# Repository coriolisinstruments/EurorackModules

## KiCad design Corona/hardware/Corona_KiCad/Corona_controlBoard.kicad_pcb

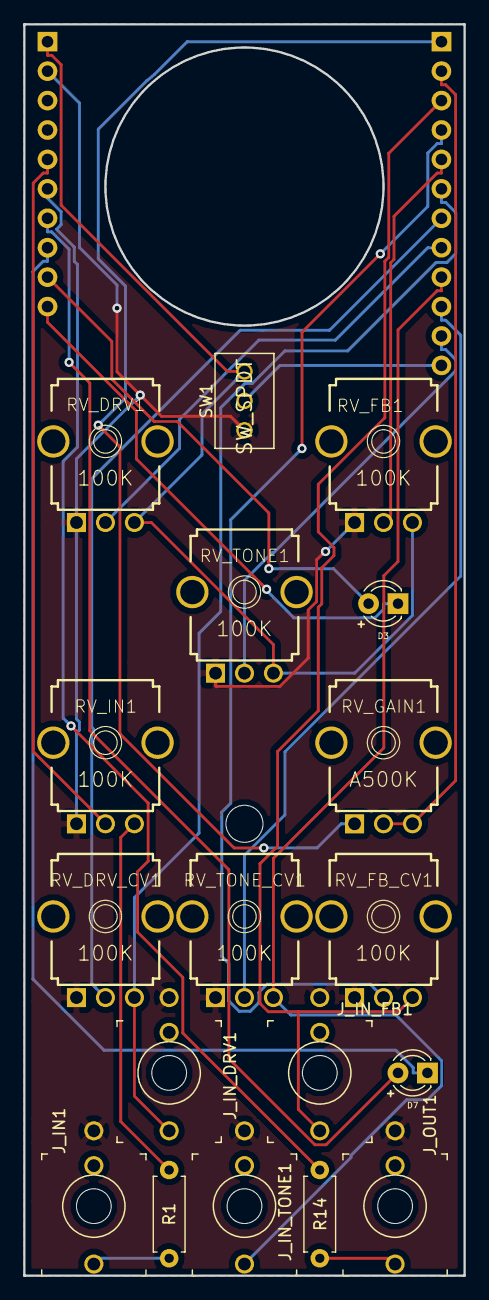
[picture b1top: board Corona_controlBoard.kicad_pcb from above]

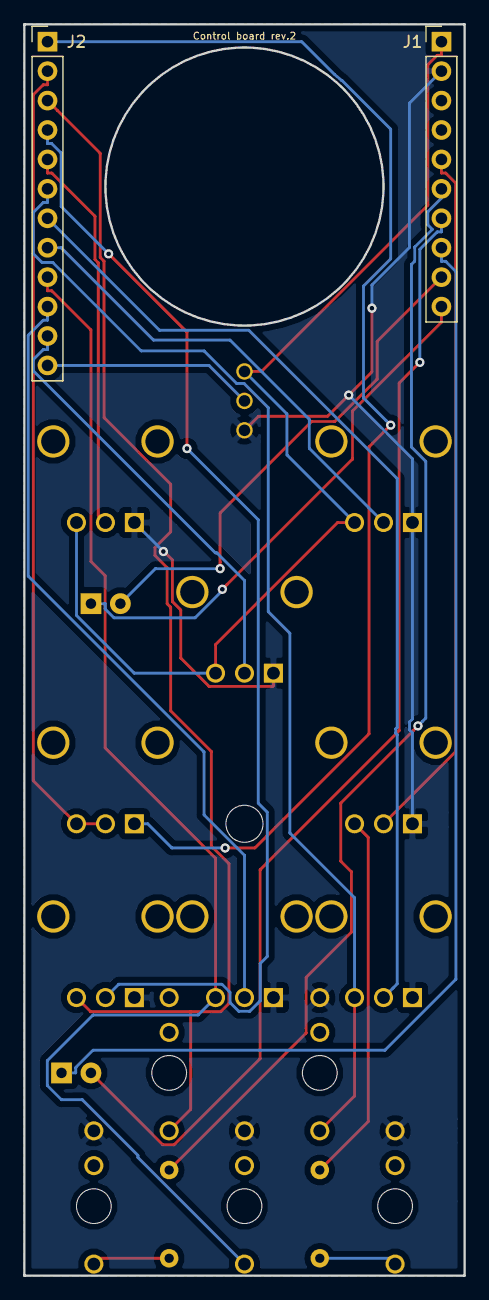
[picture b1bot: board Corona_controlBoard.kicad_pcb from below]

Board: 2 copper layers, 38.0 x 108.0 mm, 22 parts (2 on the bottom side), 23 nets.

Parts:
D3, D7: LED; LED_D3.0mm_smalltext
J1: Conn_01x10; PinHeader_1x10_P2.54mm_Vertical
J2: Conn_01x12; PinHeader_1x12_P2.54mm_Vertical
J_IN1: Audio-Jack-2_Switch; WQP-PJ301M-12_JACK
J_IN_DRV1: Audio-Jack-2_Switch; WQP-PJ301M-12_JACK
J_IN_FB1: Audio-Jack-2_Switch; WQP-PJ301M-12_JACK
J_IN_TONE1: Audio-Jack-2_Switch; WQP-PJ301M-12_JACK
J_OUT1: Audio-Jack-2_Switch; WQP-PJ301M-12_JACK
MK3: Mounting_Hole; MountingHole_3.2mm_M3
MK5: CoriolisLogo; art_Coriolis_logo_copper
R1: 47K; R_Axial_DIN0207_L6.3mm_D2.5mm_P7.62mm_Horizontal
R14: 470r; R_Axial_DIN0207_L6.3mm_D2.5mm_P7.62mm_Horizontal
RV_DRV1: 100K; 9MM_SNAP-IN_POT
RV_DRV_CV1: 100K; 9MM_SNAP-IN_POT
RV_FB1: 100K; 9MM_SNAP-IN_POT
RV_FB_CV1: 100K; 9MM_SNAP-IN_POT
RV_GAIN1: A500K; 9MM_SNAP-IN_POT
RV_IN1: 100K; 9MM_SNAP-IN_POT
RV_TONE1: 100K; 9MM_SNAP-IN_POT
RV_TONE_CV1: 100K; 9MM_SNAP-IN_POT
SW1: SW_SPDT; SUBMINI_TOGGLE

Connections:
/+12V.cb: J1.1, RV_DRV1.3, RV_FB1.3, RV_TONE1.3, SW1.3
/R.gain.1.cb: J2.1, RV_GAIN1.1
/R.gain.3.cb: J2.2, RV_GAIN1.2, RV_GAIN1.3
/audio.in.cb: J1.5, RV_IN1.2
/audio.out.cb: J1.6, R14.2
/drv.cv.in.cb: J2.6, J_IN_DRV1.1, RV_DRV_CV1.3
/drv.cv.level.cb: J2.7, RV_DRV_CV1.2
/drv.level.cb: J2.8, RV_DRV1.2
/fb.cv.in.cb: J2.3, J_IN_FB1.1, RV_FB_CV1.3
/fb.cv.level.cb: J2.4, RV_FB_CV1.2
/fb.level.cb: J2.5, RV_FB1.2
/gnd.cb: J1.2, J_IN1.2, J_IN_DRV1.2, J_IN_FB1.2, J_IN_TONE1.2, J_OUT1.2, RV_DRV1.1, RV_DRV_CV1.1, RV_FB1.1, RV_FB_CV1.1, RV_IN1.1, RV_TONE1.1, RV_TONE_CV1.1, SW1.1
/led.clip.in.cb: D7.2, J1.7
/led.clip.out.cb: D7.1, J1.8
/led.fb.in.cb: D3.2, J1.9
/led.fb.out.cb: D3.1, J1.10
/tone.cv.in.cb: J2.9, J_IN_TONE1.1, RV_TONE_CV1.3
/tone.cv.level.cb: J2.10, RV_TONE_CV1.2
/tone.level.cb: J2.11, RV_TONE1.2
/tube.gnd.cb: J2.12, SW1.2
unnamed: J_IN1.1, R1.2
unnamed: J_OUT1.1, R14.1
unnamed: R1.1, RV_IN1.3

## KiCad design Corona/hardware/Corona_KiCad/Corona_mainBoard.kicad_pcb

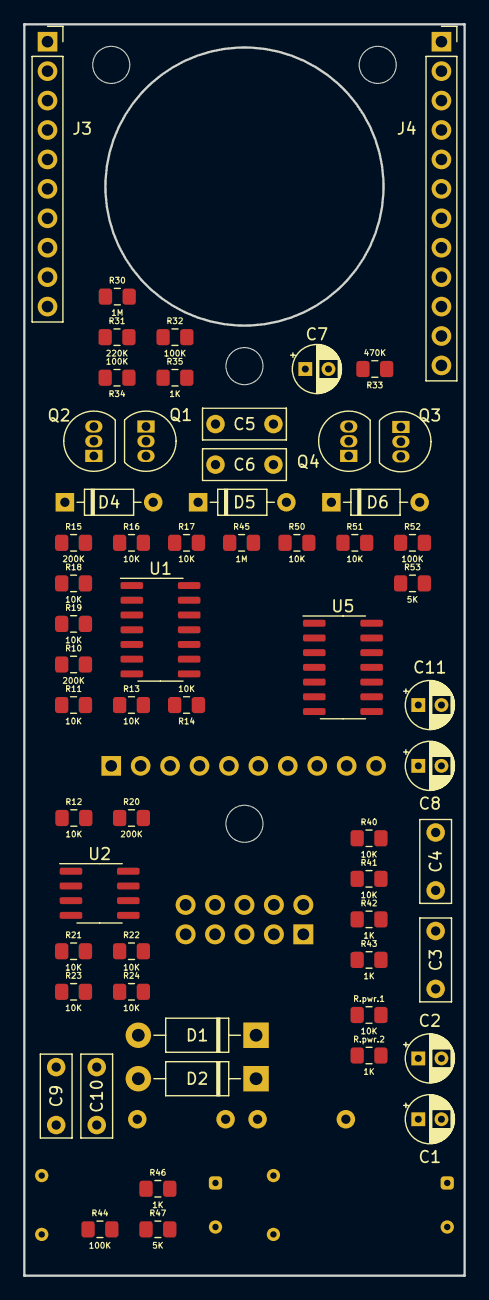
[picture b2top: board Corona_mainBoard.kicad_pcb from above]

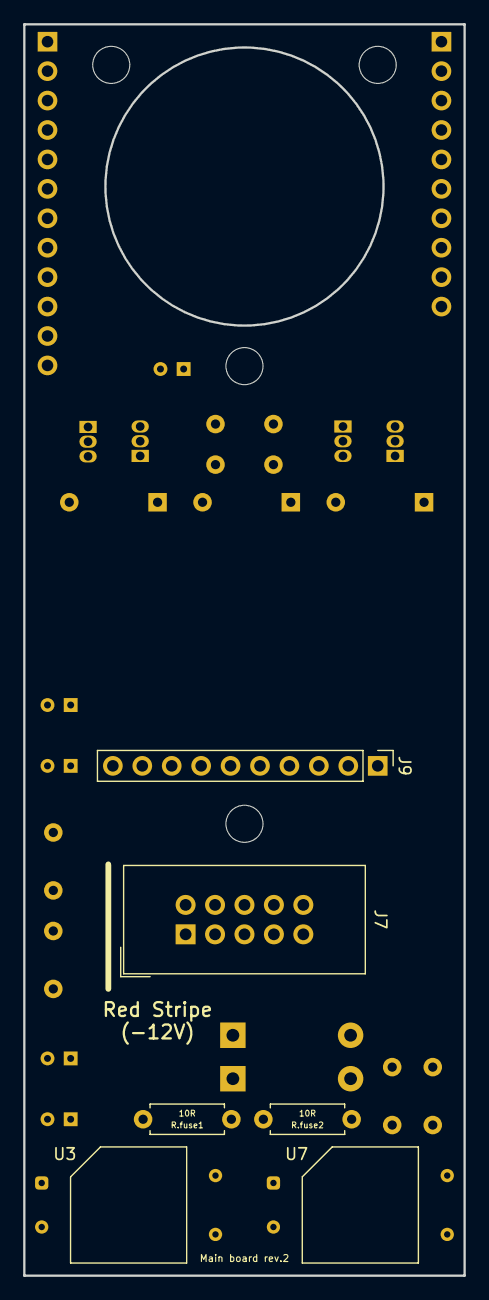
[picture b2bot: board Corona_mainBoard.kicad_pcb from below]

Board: 2 copper layers, 38.0 x 108.0 mm, 70 parts (6 on the bottom side), 55 nets, no tracks yet.

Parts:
C1, C2: 10uF (25V); CP_Radial_D4.0mm_P2.00mm
C3, C4, C10: 100nF; C_Disc_D7.0mm_W2.5mm_P5.00mm
C5, C6: 47nF; C_Disc_D7.0mm_W2.5mm_P5.00mm
C7, C8: 1uF (25V); CP_Radial_D4.0mm_P2.00mm
C9: 22nF; C_Disc_D7.0mm_W2.5mm_P5.00mm
C11: 0.22uF; CP_Radial_D4.0mm_P2.00mm
D1, D2: IN4001; D_DO-41_SOD81_P10.16mm_Horizontal
D4, D5, D6: IN4148; D_DO-35_SOD27_P7.62mm_Horizontal
J3: Conn_01x10; PinSocket_1x10_P2.54mm_Vertical
J4: Conn_01x12; PinSocket_1x12_P2.54mm_Vertical
J7: Conn_02x05_Odd_Even; IDC-Header_2x05_P2.54mm_Vertical
J9: Conn_01x10; PinHeader_1x10_P2.54mm_Vertical
MK.mb1, MK.mb2, MK.mb3, MK.mb4: Mounting_Hole; MountingHole_3.2mm_M3
Q1, Q2, Q3: BC547; TO-92_Inline
Q4: BC557; TO-92_Inline
R10, R15, R20: 200K; R_0805_2012Metric_Pad1.15x1.40mm_HandSolder_smalltext
R11, R12, R13, R14, R16, R17, R18, R19, R21, R22, R23, R24, R40, R41, R50, R51, R.pwr.1: 10K; R_0805_2012Metric_Pad1.15x1.40mm_HandSolder_smalltext
R30, R45: 1M; R_0805_2012Metric_Pad1.15x1.40mm_HandSolder_smalltext
R31: 220K; R_0805_2012Metric_Pad1.15x1.40mm_HandSolder_smalltext
R32, R34, R44, R52: 100K; R_0805_2012Metric_Pad1.15x1.40mm_HandSolder_smalltext
R33: 470K; R_0805_2012Metric_Pad1.15x1.40mm_HandSolder_smalltext
R35, R42, R43, R46, R.pwr.2: 1K; R_0805_2012Metric_Pad1.15x1.40mm_HandSolder_smalltext
R47, R53: 5K; R_0805_2012Metric_Pad1.15x1.40mm_HandSolder_smalltext
R.fuse1, R.fuse2: 10R; R_Axial_DIN0207_smalltext
U1, U5: TL074; SOIC-14_3.9x8.7mm_P1.27mm
U2: TL072; SOIC-8_3.9x4.9mm_P1.27mm
U3, U7: VTL5C; PerkinElmer_VTL5C

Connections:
/+1V: R16.1, R17.1, R21.1, R22.1, R.pwr.1.1, R.pwr.2.2, U1.12, U2.5
/+12V: C1.1, C3.1, D4.2, J3.1, J9.9, Q2.1, Q3.1, R31.2, R34.2, R.fuse1.1, R.pwr.1.2, U1.4, U2.8, U5.4
/-12V: C2.2, C4.2, J3.3, J9.8, R.fuse2.1, U1.11, U2.4, U5.11
/R.gain.1: C8.1, J4.1, U5.1
/R.gain.3: J4.2, R35.1, U5.2
/audio.in: J3.5, U5.5
/audio.out: C10.2, J3.6, J9.10, U5.13, U5.14
/cv.drv: R18.1, U1.14, U3.2
/cv.fb: R13.1, R45.1, U1.8
/cv.tone: R23.1, U2.7, U7.2
/drv.cv.in: J4.6, R15.2, U1.2
/drv.cv.level: J4.7, U1.3
/drv.level: J4.8, R17.2
/fb.cv.in: J4.3, R10.2, U1.6
/fb.cv.level: J4.4, U1.5
/fb.level: J4.5, R12.2
/gnd: C1.2, C2.1, C3.2, C4.1, C11.2, D1.2, D2.1, J3.2, J7.3, J7.4, J7.5, J7.6, J7.7, J7.8, J9.7, R14.1, R19.1, R24.1, R32.1, R40.2, R44.1, R46.1, R47.1, R52.1, R53.1, R.pwr.2.1, U5.3, U5.10, U7.3
/led.clip.in: D6.1, J3.7, Q4.3
/led.clip.out: J3.8, Q4.1, R53.2
/led.fb.in: C9.1, J3.9, Q1.3, R46.2
/led.fb.out: J3.10, R47.2
/tone.cv.in: J4.9, R20.2, U2.2
/tone.cv.level: J4.10, U2.3
/tone.level: J4.11, R22.2
/tube.1: C6.2, J9.1, R31.1
/tube.2: C5.1, J9.2, R30.2
/tube.3: J9.3, U3.4
/tube.6: C7.1, J9.4, R34.1
/tube.7: C6.1, J9.5, R33.2
/tube.8: J4.12, J9.6, R30.1, R33.1, U3.3
/tube.in: C5.2, C9.2, R41.1, U5.7
/tube.out: C8.2, R42.2, R50.2
unnamed: C7.2, R35.2
unnamed: C10.1, U7.4
unnamed: C11.1, Q3.3, R51.2, R52.2
unnamed: D1.1, J7.9, J7.10, R.fuse1.2
unnamed: D2.2, J7.1, J7.2, R.fuse2.2
unnamed: D4.1, D5.2
unnamed: D5.1, D6.2
unnamed: Q1.1, R43.1, U5.8, U5.12
unnamed: Q1.2, Q2.3
unnamed: Q2.2, R45.2
unnamed: Q3.2, R50.1
unnamed: Q4.2, R51.1
unnamed: R10.1, R11.2, U1.7
unnamed: R11.1, R12.1, U1.10
unnamed: R13.2, R14.2, U1.9
unnamed: R15.1, R16.2, U1.1
unnamed: R18.2, R19.2, U1.13
unnamed: R20.1, R21.2, U2.1
unnamed: R23.2, R24.2, U2.6
unnamed: R32.2, U3.1
unnamed: R40.1, R41.2, U5.6
unnamed: R42.1, R43.2, U5.9
unnamed: R44.2, U7.1

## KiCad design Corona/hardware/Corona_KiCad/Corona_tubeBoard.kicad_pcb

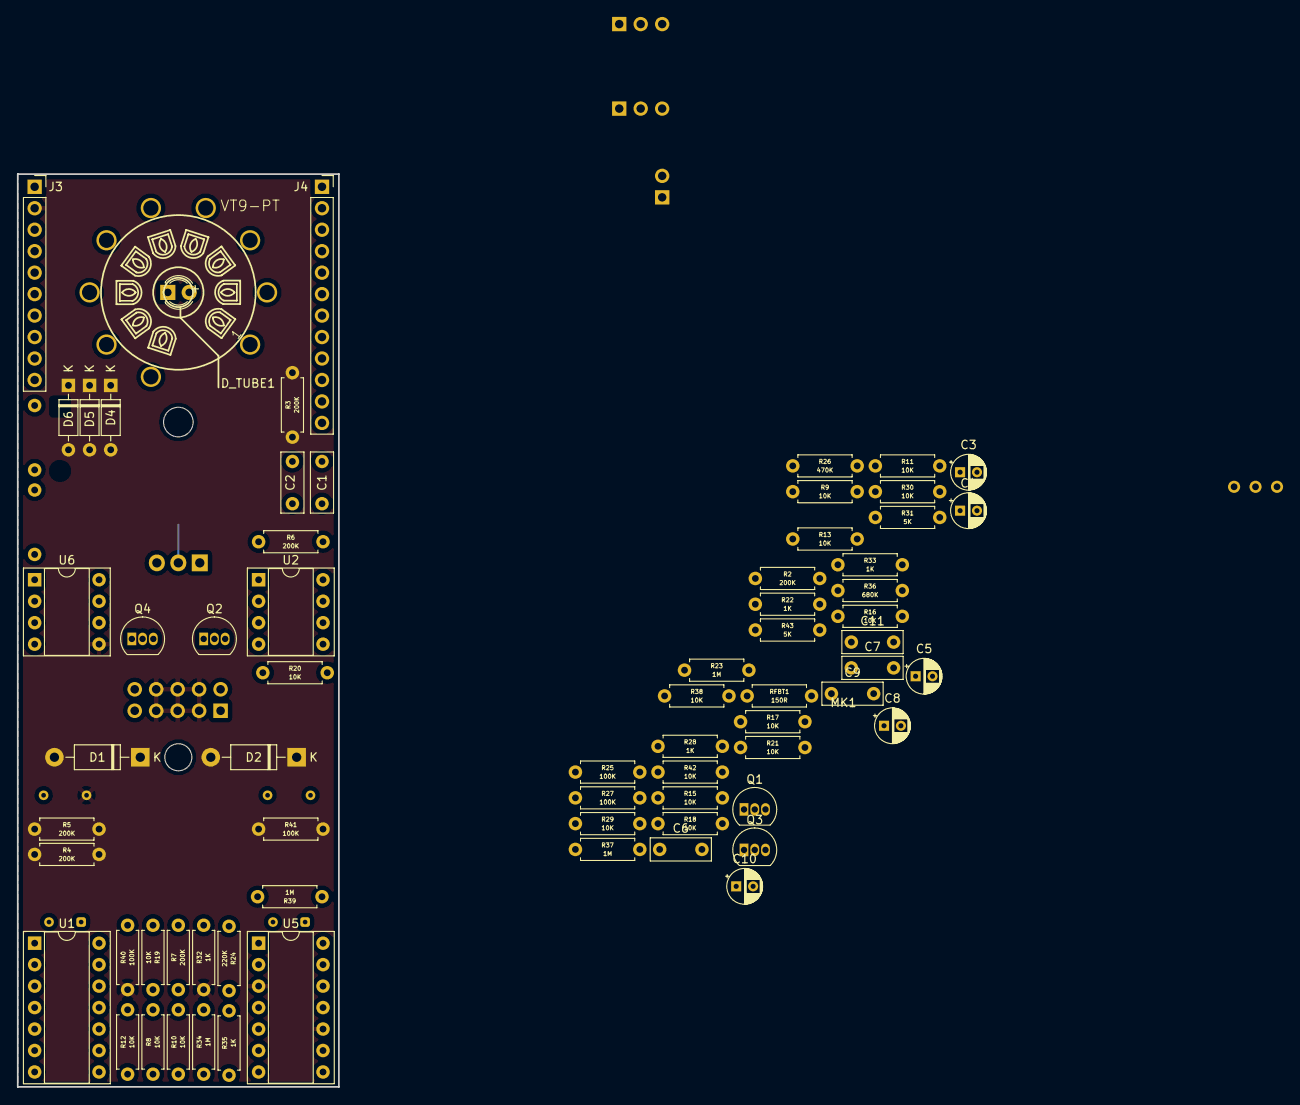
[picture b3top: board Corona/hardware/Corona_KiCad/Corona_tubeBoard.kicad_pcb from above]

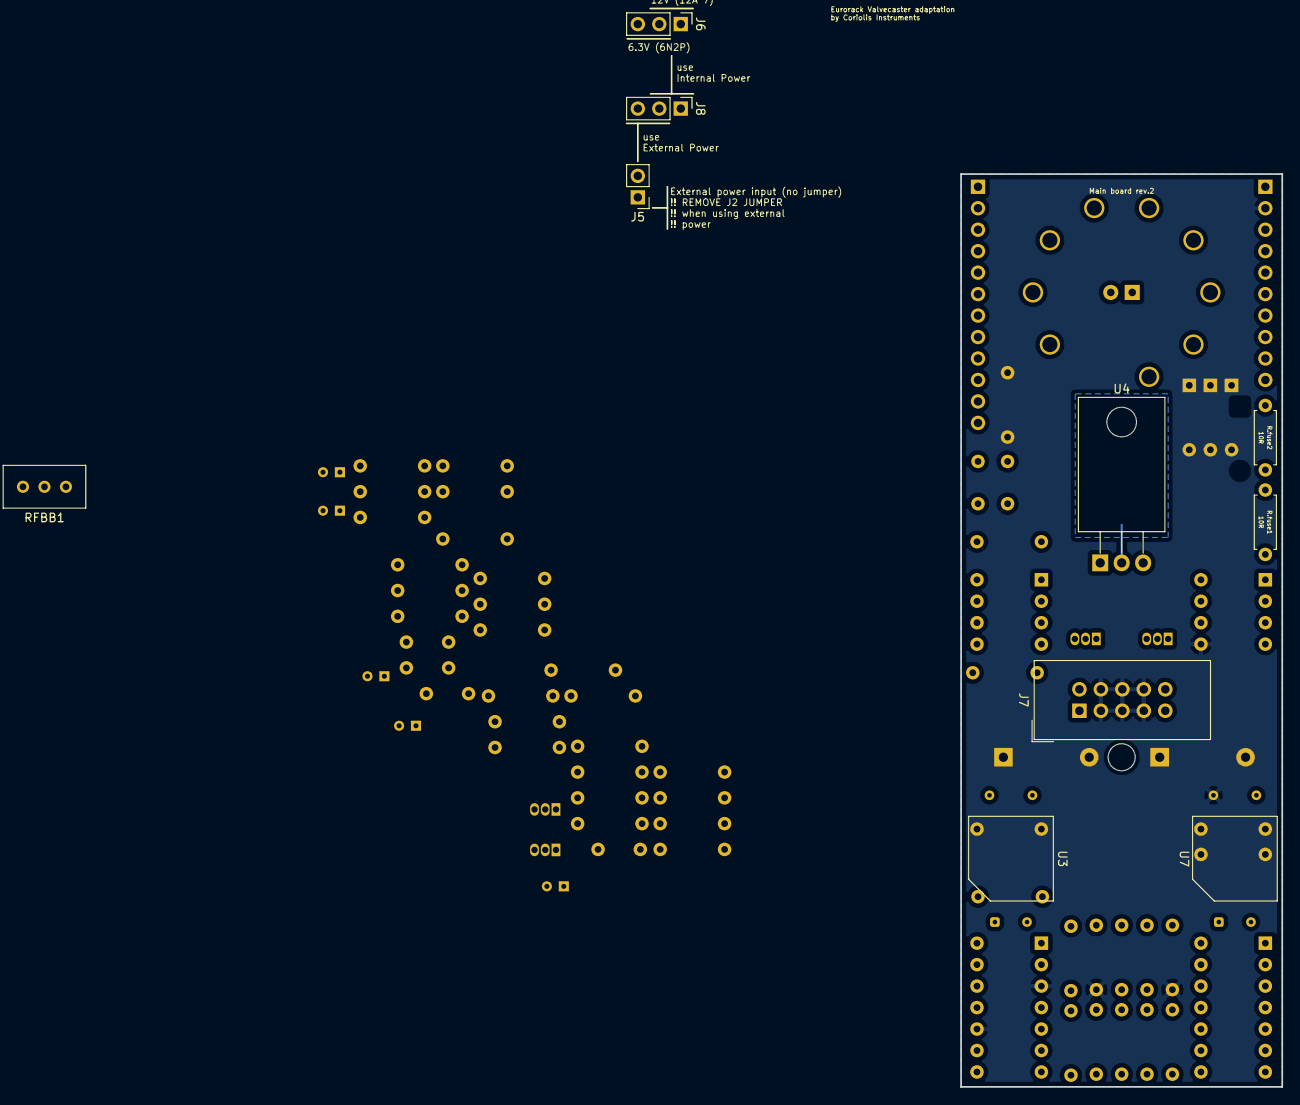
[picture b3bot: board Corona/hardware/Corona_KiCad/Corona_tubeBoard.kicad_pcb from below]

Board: 2 copper layers, 38.0 x 108.0 mm, 82 parts (11 on the bottom side), 67 nets.

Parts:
C1, C2: 47nF; C_Disc_D7.0mm_W2.5mm_P5.00mm
C3, C4: 10uF (25V); CP_Radial_D4.0mm_P2.00mm
C5, C8: 1uF (25V); CP_Radial_D4.0mm_P2.00mm
C6, C7, C11: 100nF; C_Disc_D7.0mm_W2.5mm_P5.00mm
C9: 22nF; C_Disc_D7.0mm_W2.5mm_P5.00mm
C10: 0.22uF; CP_Radial_D4.0mm_P2.00mm
D1, D2: IN4001; D_DO-41_SOD81_P10.16mm_Horizontal
D4, D5, D6: IN4148; D_DO-35_SOD27_P7.62mm_Horizontal
D_TUBE1: LED; LED_D3.0mm
J3: Conn_01x10; PinSocket_1x10_P2.54mm_Vertical
J4: Conn_01x12; PinSocket_1x12_P2.54mm_Vertical
J5: Conn_01x02_Male; PinHeader_1x02_P2.54mm_Vertical
J6, J8: Conn_01x03_Male; PinHeader_1x03_P2.54mm_Vertical
J7: Conn_02x05_Odd_Even; IDC-Header_2x05_P2.54mm_Vertical
MK1: Mounting_Hole; MountingHole_3.2mm_M3
MK5: CoriolisLogo; art_Coriolis_logo_copper
Q1, Q2, Q3: BC547; TO-92_Inline
Q4: BC557; TO-92_Inline
R2, R3, R4, R5, R6, R7: 200K; R_Axial_DIN0207_smalltext
R8, R9, R10, R11, R12, R13, R15, R16, R17, R18, R19, R20, R21, R29, R30, R38, R42: 10K; R_Axial_DIN0207_smalltext
R22, R28, R32, R33, R35: 1K; R_Axial_DIN0207_smalltext
R23, R34, R37, R39: 1M; R_Axial_DIN0207_smalltext
R24: 220K; R_Axial_DIN0207_smalltext
R25, R27, R40, R41: 100K; R_Axial_DIN0207_smalltext
R26: 470K; R_Axial_DIN0207_smalltext
R31, R43: 5K; R_Axial_DIN0207_smalltext
R36: 680K; R_Axial_DIN0207_smalltext
R.fuse1, R.fuse2: 10R; R_Axial_DIN0207_smalltext
RFBB1: POT_TRIM; Potentiometer_Bourns_3296W_Vertical
RFBT1: 150R; R_Axial_DIN0207_smalltext
SX1: VT9-PT; belton-engineering-VT9-PT
U1, U5: TL074; DIP-14_W7.62mm_Socket
U2, U6: TL072; DIP-8_W7.62mm_Socket
U3, U7: VTL5C; PerkinElmer_VTL5C
U4: LM337_TO220; TO-220-3_Horizontal_TabDown

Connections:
/+1V: R8.1, R9.1, R12.1, R13.1, R21.1, R22.2, U1.12, U2.5
/+12V: C3.1, C6.1, D4.2, J3.1, Q2.1, Q3.1, R21.2, R24.2, R27.2, R.fuse1.1, U1.4, U2.8, U5.4, U6.8
/-6.3V: J6.3, RFBT1.2, U4.3
/-12V: C4.2, C7.2, J3.3, J6.1, R.fuse2.1, U1.11, U2.4, U4.2, U5.11, U6.4
/R.gain.1: C8.1, J4.1, U5.1
/R.gain.3: J4.2, R28.1, U5.2
/audio.in: J3.5, U5.5
/audio.out: C11.2, J3.6, R39.1, U5.13, U5.14
/cv.drv: R19.1, U1.14, U3.2
/cv.fb: R18.1, R34.1, U1.8
/cv.tone: R20.1, U2.7, U7.2
/drv.cv.in: J4.6, R2.2
/drv.cv.level: J4.7, U1.3
/drv.level: J4.8, R8.2
/fb.cv.in: J4.3, R4.2
/fb.cv.level: J4.4, U1.5
/fb.level: J4.5, R11.2
/gnd: C3.2, C4.1, C6.2, C7.1, C10.2, D1.2, D2.1, J3.2, J7.3, J7.4, J7.5, J7.6, J7.7, J7.8, J8.1, R15.1, R16.1, R17.1, R22.1, R25.1, R29.2, R31.1, R32.1, R36.2, R37.1, R40.1, R41.1, R43.1, RFBB1.1, RFBB1.2, U5.3, U5.10, U6.5, U7.3
/led.clip.in: D6.1, J3.7, Q4.3
/led.clip.out: J3.8, Q4.1, R43.2
/led.fb.in: C9.1, J3.9, Q1.3, R32.2
/led.fb.out: J3.10, R31.2
/tone.cv.in: J4.9, R3.2
/tone.cv.level: J4.10, U2.3
/tone.level: J4.11, R9.2
/tube.1: C2.2, R24.1, SX1.1
/tube.2: C1.1, R23.2, SX1.2
/tube.3: SX1.3, U3.4
/tube.4: J5.1, J6.2, SX1.4
/tube.6: C5.1, R27.1, SX1.6
/tube.7: C2.1, R26.2, SX1.7
/tube.8: J4.12, R23.1, R26.1, SX1.8, U3.3
/tube.in: C1.2, C9.2, R30.1, U5.7
/tube.out: C8.2, R33.2, R38.2
unnamed: C5.2, R28.2
unnamed: C10.1, Q3.3, R41.2, R42.2
unnamed: C11.1, U7.4
unnamed: D1.1, J7.9, J7.10, R.fuse1.2
unnamed: D2.2, J7.1, J7.2, R.fuse2.2
unnamed: D4.1, D5.2
unnamed: D5.1, D6.2
unnamed: D_TUBE1.1, U6.1
unnamed: D_TUBE1.2, R36.1, U6.2
unnamed: J5.2, J8.3
unnamed: J8.2, SX1.5
unnamed: Q1.1, R35.1, U5.8, U5.12
unnamed: Q1.2, Q2.3
unnamed: Q2.2, R34.2
unnamed: Q3.2, R38.1
unnamed: Q4.2, R42.1
unnamed: R2.1, R5.2, U1.2
unnamed: R3.1, R6.2, U2.2
unnamed: R4.1, R7.2, U1.6
unnamed: R10.1, R11.1, U1.10
unnamed: R7.1, R10.2, U1.7
unnamed: R5.1, R12.2, U1.1
unnamed: R6.1, R13.2, U2.1
unnamed: R15.2, R18.2, U1.9
unnamed: R16.2, R19.2, U1.13
unnamed: R17.2, R20.2, U2.6
unnamed: R25.2, U3.1
unnamed: R29.1, R30.2, U5.6
unnamed: R33.1, R35.2, U5.9
unnamed: R37.2, R39.2, U6.3
unnamed: R40.2, U7.1
unnamed: RFBB1.3, RFBT1.1, U4.1
unnamed: U6.6, U6.7

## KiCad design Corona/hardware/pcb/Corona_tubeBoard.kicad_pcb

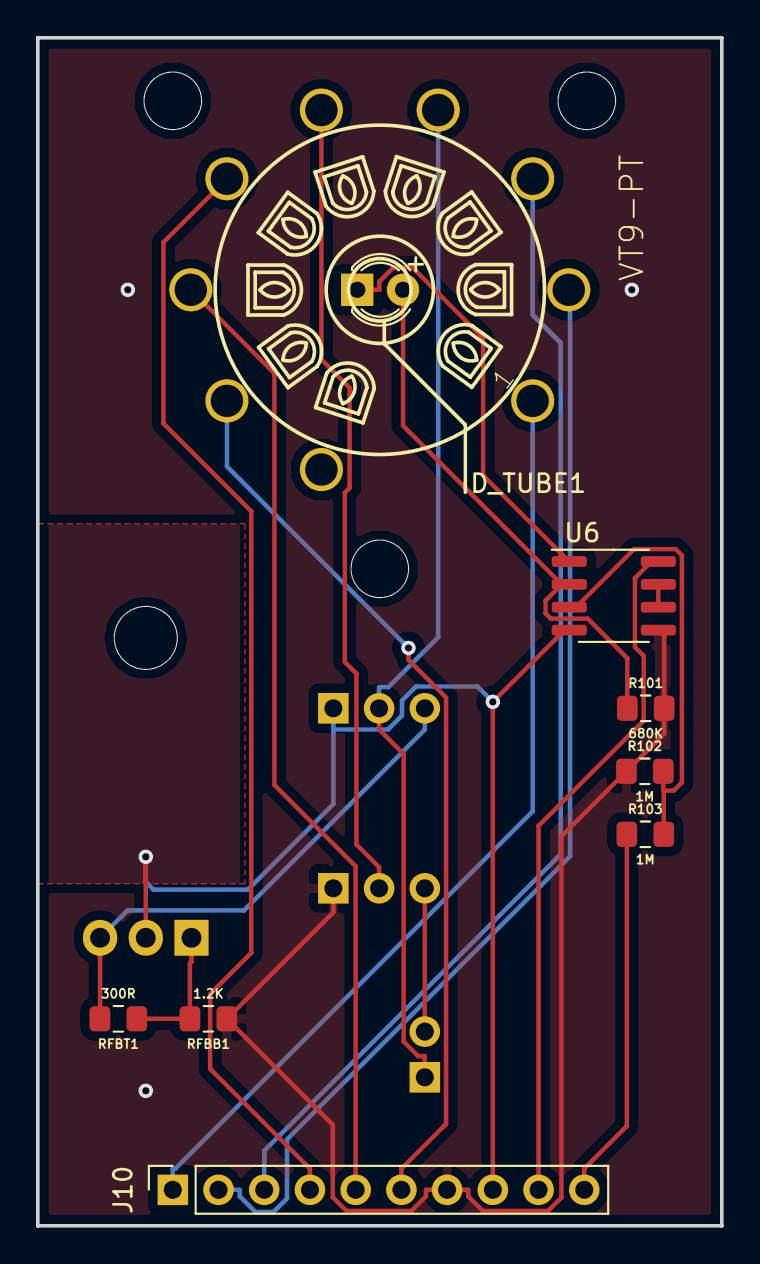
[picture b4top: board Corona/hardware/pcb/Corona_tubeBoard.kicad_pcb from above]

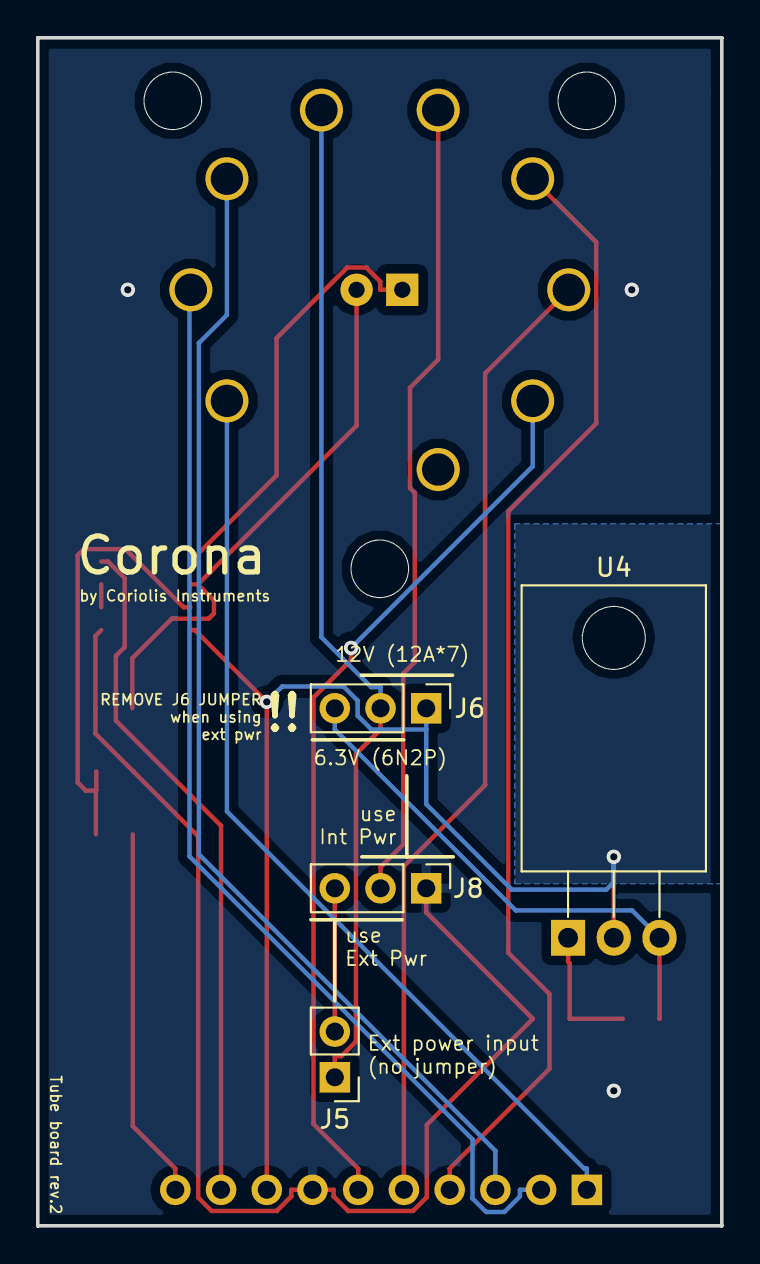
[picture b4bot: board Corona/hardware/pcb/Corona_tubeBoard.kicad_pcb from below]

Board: 2 copper layers, 38.0 x 66.0 mm, 17 parts (5 on the bottom side), 19 nets.

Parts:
D_TUBE1: LED; LED_D3.0mm
J5: Conn_01x02_Male; PinHeader_1x02_P2.54mm_Vertical
J6, J8: Conn_01x03_Male; PinHeader_1x03_P2.54mm_Vertical
J10: Conn_01x10; PinSocket_1x10_P2.54mm_Vertical
MK5: CoriolisLogo; art_Coriolis_logo_copper
MK.tb1, MK.tb2, MK.tb3: Mounting_Hole; MountingHole_3.2mm_M3
R101: 680K; R_0805_2012Metric_Pad1.15x1.40mm_HandSolder_smalltext
R102, R103: 1M; R_0805_2012Metric_Pad1.15x1.40mm_HandSolder_smalltext
RFBB1: 1.2K; R_0805_2012Metric_Pad1.15x1.40mm_HandSolder_smalltext
RFBT1: 300R; R_0805_2012Metric_Pad1.15x1.40mm_HandSolder_smalltext
SX1: VT9-PT; belton-engineering-VT9-PT
U4: LM337_TO220; TO-220-3_Horizontal_TabDown
U6: TL072; SOIC-8_3.9x4.9mm_P1.27mm

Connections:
/+12V.tb: J10.9, U6.8
/-6.3V.tb: J6.3, RFBT1.2, U4.3
/-12V.tb: J6.1, J10.8, U4.2, U6.4
/audio.out.tb: J10.10, R103.1
/gnd.tb: J8.1, J10.7, R101.2, R102.1, RFBB1.1, U6.5
/tube.1.tb: J10.1, SX1.1
/tube.2.tb: J10.2, SX1.2
/tube.3.tb: J10.3, SX1.3
/tube.4.tb: J5.1, J6.2, SX1.4
/tube.6.tb: J10.4, SX1.6
/tube.7.tb: J10.5, SX1.7
/tube.8.tb: J10.6, SX1.8
unnamed: D_TUBE1.1, U6.1
unnamed: D_TUBE1.2, R101.1, U6.2
unnamed: J5.2, J8.3
unnamed: J8.2, SX1.5
unnamed: R102.2, R103.2, U6.3
unnamed: RFBB1.2, RFBT1.1, U4.1
unnamed: U6.6, U6.7
